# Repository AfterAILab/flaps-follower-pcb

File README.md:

# AfterAI Flaps Follower PCB

This repository is part of the [AfterAI Flaps](https://afterai.dev/flaps) project.
You can purchase AfterAI Flaps goods at [AfterAI's online store](https://shop.afterai.dev). 

## How to Order a PCB

You can order a PCB from [JLCPCB](https://jlcpcb.com).
You need to create a gerber file from the KiCad project. You can use the [Fabrication Toolkit](https://github.com/afterai-dev/flaps-fabrication-toolkit) to create the gerber file.

## Software Repository

- [flaps-avr](https://github.com/AfterAILab/flaps-avr) - Firmware for the AVR microcontroller

## How to Upload Program to the PCB

https://afterai.dev/Zettelkasten/How+to+Upload+Program+to+AfterAI+Flaps+Follower

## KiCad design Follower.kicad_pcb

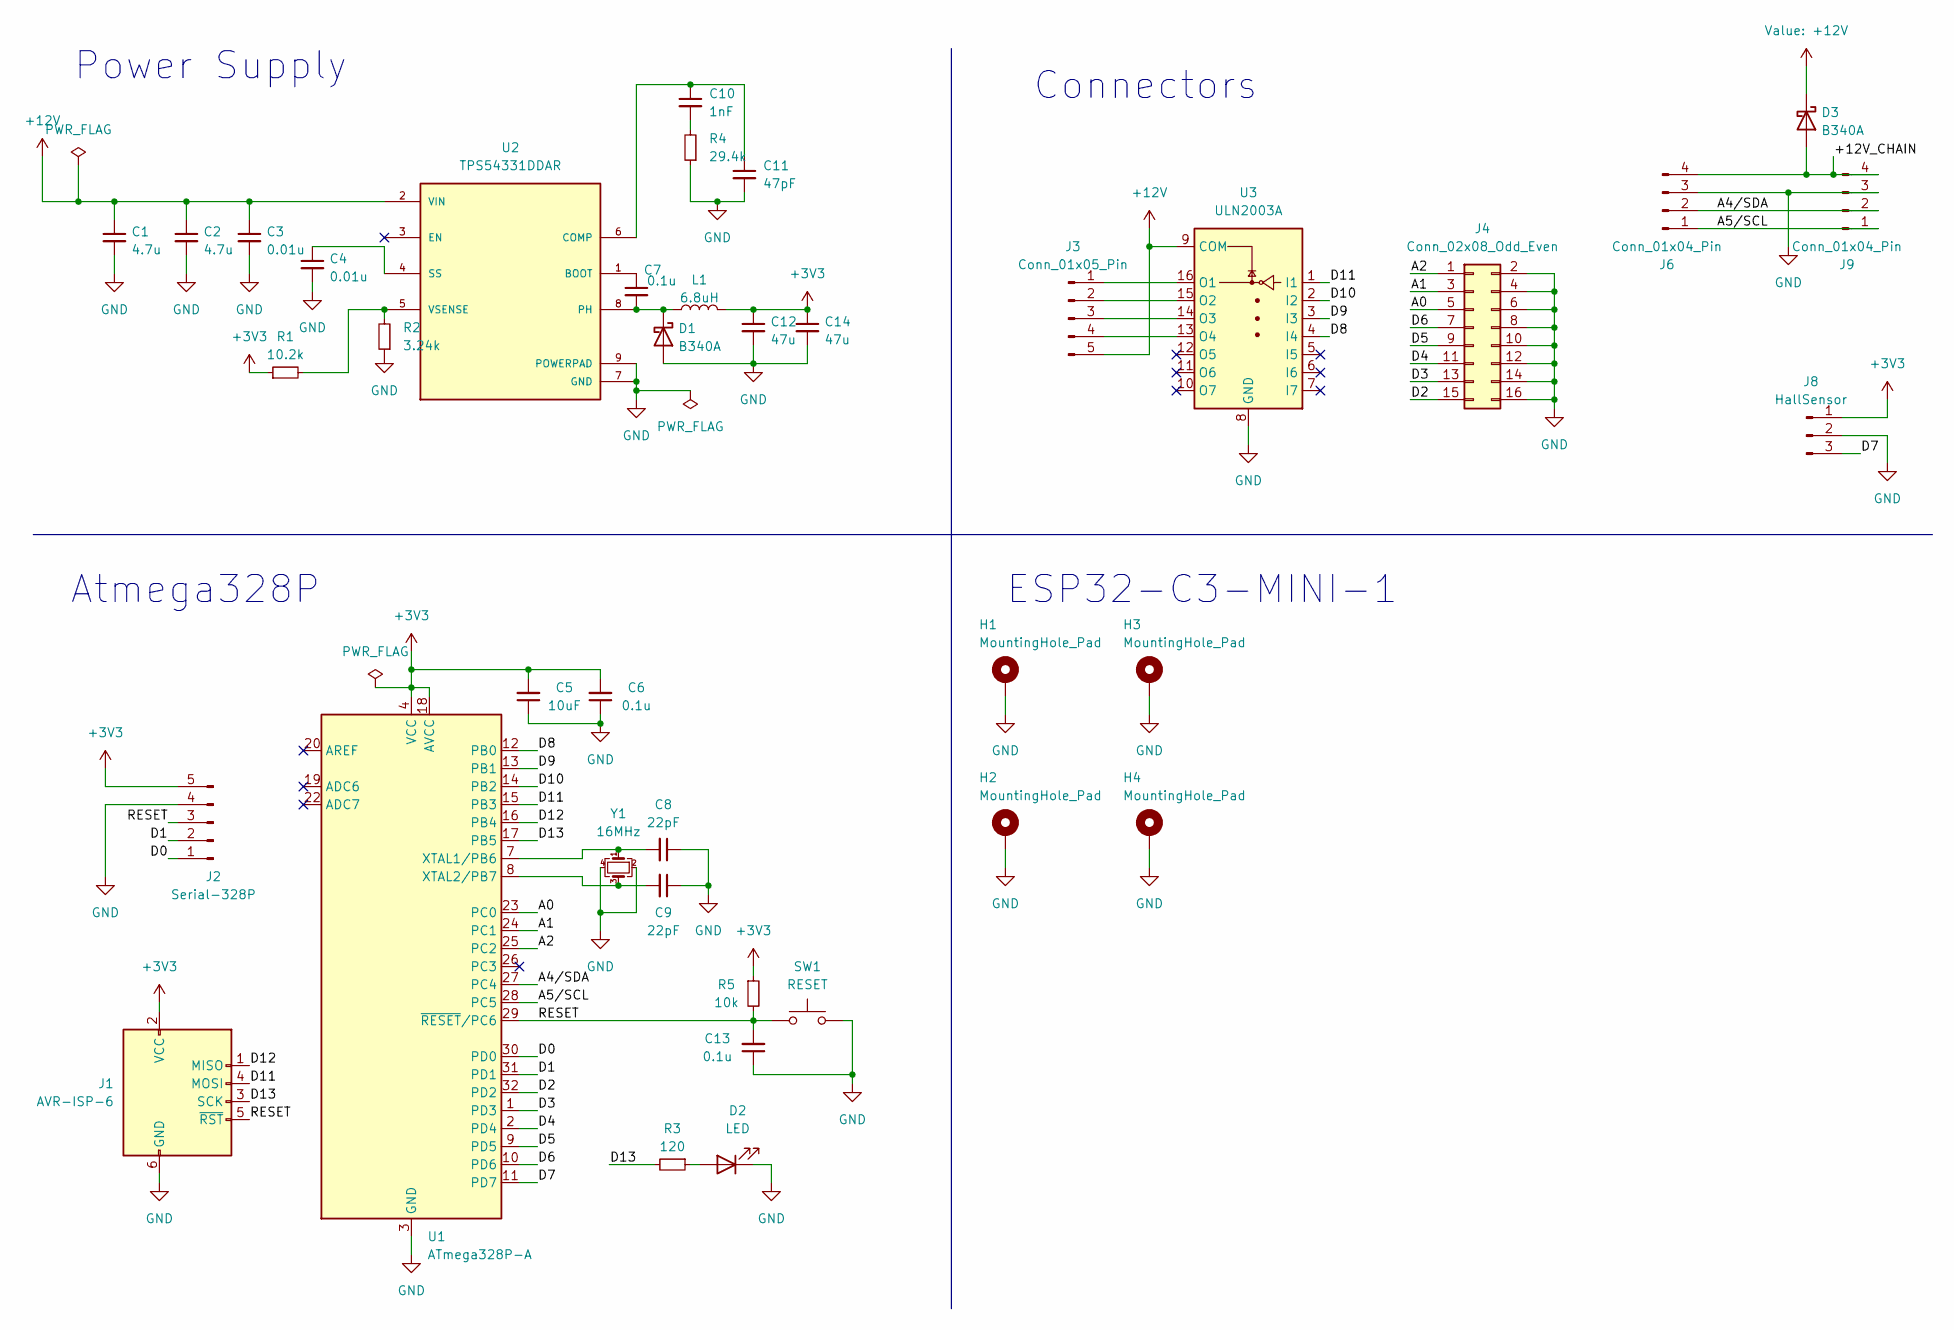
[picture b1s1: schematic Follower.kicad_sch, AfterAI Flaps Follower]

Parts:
C1, C2: 4.7u; C_0805_2012Metric; LCSC C77077
C3, C4: 0.01u; C_0603_1608Metric; LCSC C77053
C5: 10uF; C_0805_2012Metric; LCSC C440198
C6, C7, C13: 0.1u; C_0402_1005Metric; LCSC C307331
C8, C9: 22pF; C_0402_1005Metric; LCSC C1555
C10: 1nF; C_0603_1608Metric; LCSC C1636
C11: 47pF; C_0402_1005Metric; LCSC C60137
C12, C14: 47u; C_0603_1608Metric; LCSC C140782
D1, D3: B340A; D_SMA; LCSC C3018525
D2: LED; LED_0805_2012Metric; LCSC C2297
H1, H2, H3, H4: MountingHole_Pad; MountingHole_3.2mm_M3_DIN965_Pad
J1: AVR-ISP-6; PinHeader_2x03_P2.54mm_Vertical; LCSC C65114
J2: Serial-328P; PinHeader_1x05_P2.54mm_Vertical; LCSC C492404
J3: Conn_01x05_Pin; JST_XH_B5B-XH-AM_1x05_P2.50mm_Vertical; LCSC C161872
J4: Conn_02x08_Odd_Even; PinHeader_2x08_P2.54mm_Vertical; LCSC C5383108
J6, J9: Conn_01x04_Pin; JST_XH_B4B-XH-AM_1x04_P2.50mm_Vertical; LCSC C161871
J8: HallSensor; JST_XH_B3B-XH-AM_1x03_P2.50mm_Vertical; LCSC C161870
L1: 6.8uH; L_Sunlord_MWSA0603S; LCSC C408449
R1: 10.2k; R_0402_1005Metric; LCSC C11660
R2: 3.24k; R_0603_1608Metric; LCSC C22994
R3: 120; R_0402_1005Metric; LCSC C25079
R4: 29.4k; R_0402_1005Metric; LCSC C327356
R5: 10k; R_0402_1005Metric; LCSC C25744
SW1: RESET; SW_SPST_SKQG_WithStem; LCSC C318884
U1: ATmega328P-A; TQFP-32_7x7mm_P0.8mm; LCSC C14877
U2: TPS54331DDAR; CONV_TPS54331DDAR; PARTREV F; LCSC C90761
U3: ULN2003A; SOIC-16_3.9x9.9mm_P1.27mm; LCSC C7512
Y1: 16MHz; Crystal_SMD_3225-4Pin_3.2x2.5mm; LCSC C13738

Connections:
+3V3: C5.2, C6.2, C12.1, C14.1, J1.2 (VCC), J2.5, J8.1, L1.2, R1.1, R5.1, U1.4 (VCC), U1.6 (VCC), U1.18 (AVCC)
+12V: C1.1, C2.1, C3.1, D3.1 (K), J3.5, U2.2 (VIN), U3.9 (COM)
/+12V_CHAIN: D3.2 (A), J6.4, J9.4
/A0: J4.5, U1.23 (PC0)
/A1: J4.3, U1.24 (PC1)
/A2: J4.1, U1.25 (PC2)
/A4/SDA: J6.2, J9.2, U1.27 (PC4)
/A5/SCL: J6.1, J9.1, U1.28 (PC5)
/D0: J2.1, U1.30 (PD0)
/D1: J2.2, U1.31 (PD1)
/D2: J4.15, U1.32 (PD2)
/D3: J4.13, U1.1 (PD3)
/D4: J4.11, U1.2 (PD4)
/D5: J4.9, U1.9 (PD5)
/D6: J4.7, U1.10 (PD6)
/D7: J8.3, U1.11 (PD7)
/D8: U1.12 (PB0), U3.4 (I4)
/D9: U1.13 (PB1), U3.3 (I3)
/D10: U1.14 (PB2), U3.2 (I2)
/D11: J1.4 (MOSI), U1.15 (PB3), U3.1 (I1)
/D12: J1.1 (MISO), U1.16 (PB4)
/D13: J1.3 (SCK), R3.2, U1.17 (PB5)
/RESET: C13.2, J1.5 (~RST), J2.3, R5.2, SW1.1, U1.29 (~RESET/PC6)
GND: C1.2, C2.2, C3.2, C4.2, C5.1, C6.1, C8.1, C9.1, C11.2, C12.2, C13.1, C14.2, D1.2 (A), D2.1 (K), H1.1, H2.1, H3.1, H4.1, J1.6 (GND), J2.4, J4.2, J4.4, J4.6, J4.8, J4.10, J4.12, J4.14, J4.16, J6.3, J8.2, J9.3, R2.1, R4.1, SW1.2, U1.3 (GND), U1.5 (GND), U1.21 (GND), U2.7 (GND), U2.9 (POWERPAD), U3.8 (GND), Y1.2, Y1.4
unnamed: C10.2, R4.2
unnamed: C7.2, D1.1 (K), L1.1, U2.8 (PH)
unnamed: D2.2 (A), R3.1
unnamed: J3.1, U3.16 (O1)
unnamed: J3.2, U3.15 (O2)
unnamed: J3.3, U3.14 (O3)
unnamed: J3.4, U3.13 (O4)
unnamed: C8.2, U1.7 (XTAL1/PB6), Y1.1
unnamed: C9.2, U1.8 (XTAL2/PB7), Y1.3
unnamed: C7.1, U2.1 (BOOT)
unnamed: C10.1, C11.1, U2.6 (COMP)
unnamed: C4.1, U2.4 (SS)
unnamed: R1.2, R2.2, U2.5 (VSENSE)

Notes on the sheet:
Connectors
Power Supply
ESP32-C3-MINI-1
Atmega328P

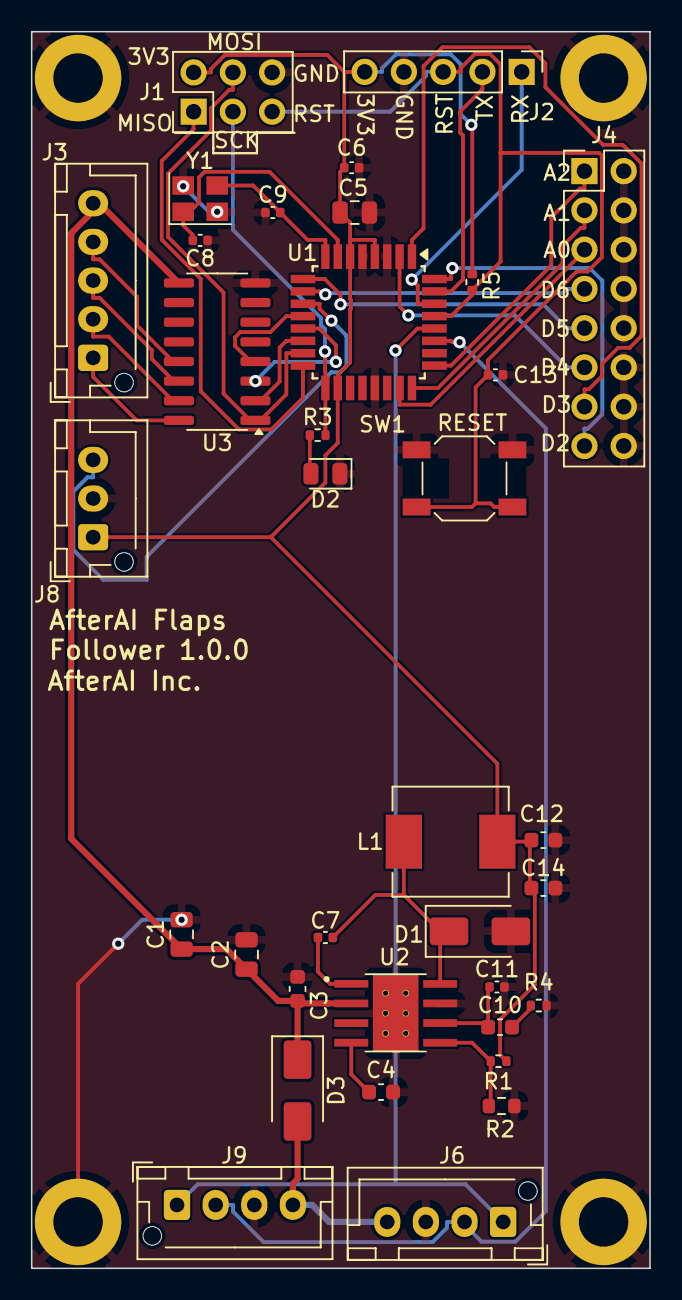
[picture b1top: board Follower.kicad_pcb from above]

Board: 2 copper layers, 40.0 x 80.0 mm, 39 parts (0 on the bottom side), 37 nets.

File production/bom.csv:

Designator,Footprint,Quantity,Value,LCSC Part #
"C1, C2",0805,2,4.7u, C77077
C10,0603,1,1nF,C1636
C11,0402,1,47pF,C60137
"C12, C14",0603,2,47u,C140782
"C13, C6, C7",0402,3,0.1u,C307331
"C3, C4",0603,2,0.01u,C77053
C5,0805,1,10uF,C440198
"C8, C9",0402,2,22pF,C1555
"D1, D3",D_SMA,2,B340A,C3018525
D2,0805,1,LED,C2297
J1,PinHeader_2x03_P2.54mm_Vertical,1,AVR-ISP-6,C65114
J2,PinHeader_1x05_P2.54mm_Vertical,1,Serial-328P,C492404
J3,JST_XH_B5B-XH-AM_1x05_P2.50mm_Vertical,1,Conn_01x05_Pin,C161872
J4,PinHeader_2x08_P2.54mm_Vertical,1,Conn_02x08_Odd_Even,C5383108
"J6, J9",JST_XH_B4B-XH-AM_1x04_P2.50mm_Vertical,2,Conn_01x04_Pin,C161871
J8,JST_XH_B3B-XH-AM_1x03_P2.50mm_Vertical,1,HallSensor, C161870
L1,L_Sunlord_MWSA0603S,1,6.8uH,C408449
R1,0402,1,10.2k,C11660
R2,0603,1,3.24k,C22994
R3,0402,1,120,C25079
R4,0402,1,29.4k,C327356
R5,0402,1,10k,C25744
SW1,SW_SPST_SKQG_WithStem,1,RESET,C318884
U1,TQFP-32_7x7mm_P0.8mm,1,ATmega328P-A,C14877
U2,CONV_TPS54331DDAR,1,TPS54331DDAR,C90761
U3,SOIC-16_3.9x9.9mm_P1.27mm,1,ULN2003A,C7512
Y1,Crystal_SMD_3225-4Pin_3.2x2.5mm,1,16MHz,C13738

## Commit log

2024-09-24 1.0.0
